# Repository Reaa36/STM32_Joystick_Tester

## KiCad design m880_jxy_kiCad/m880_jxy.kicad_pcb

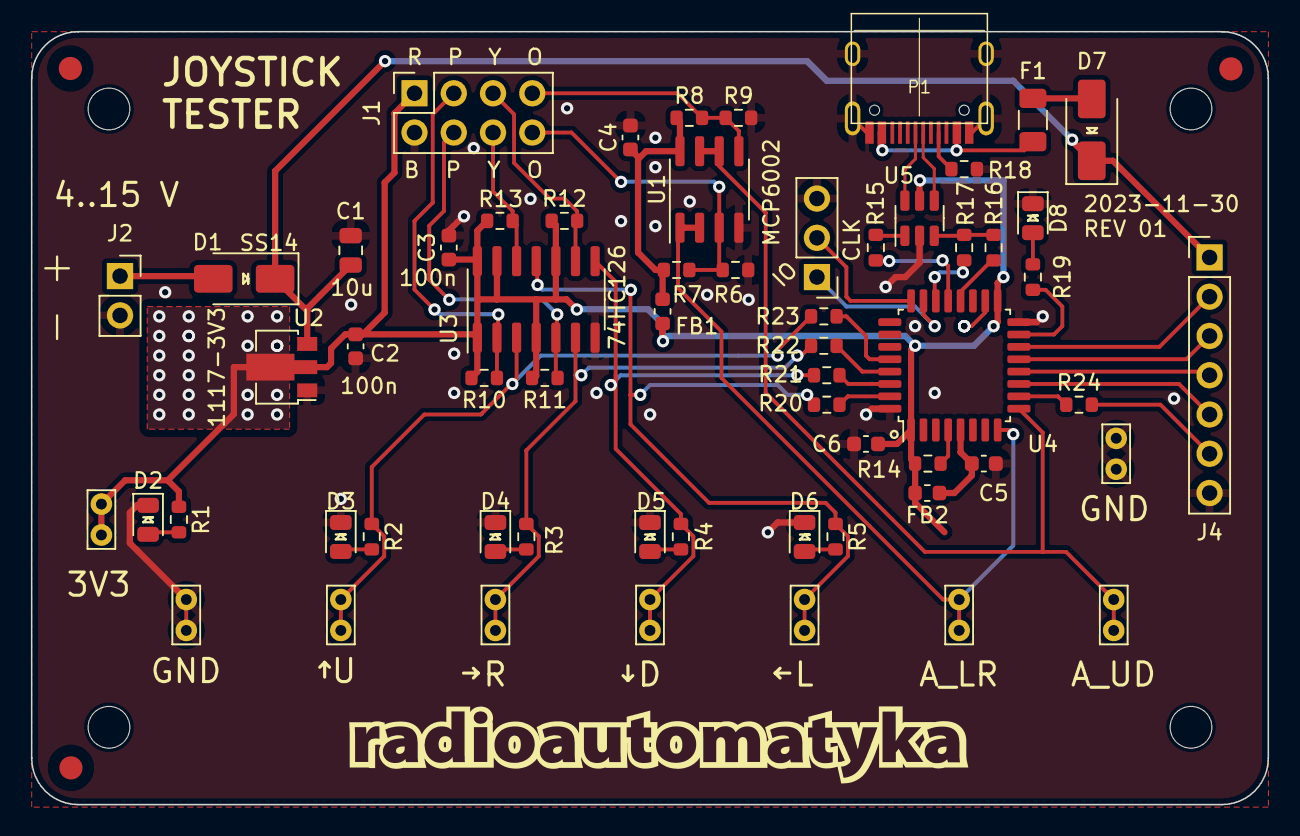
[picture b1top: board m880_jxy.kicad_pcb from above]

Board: 2 copper layers, 80.0 x 50.0 mm, 67 parts (0 on the bottom side), 48 nets.

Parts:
C1: 10u; C_0805_2012Metric
C2, C3, C4, C5, C6: 100n; C_0603_1608Metric
D1, D7: SS14; D_SMA
D2, D3, D4, D5, D6, D8: KT-0805G; LED_0805_2012Metric
F1: Polyfuse; Fuse_1206_3216Metric
FB1, FB2: GZ1608D601TF; L_0603_1608Metric
FID1, FID2, FID3: Fiducial; Fiducial_1.5mm_Mask3mm
H1, H2, H3, H4: MountingHole; MountingHole_2.7mm_M2.5
J1: 280384-2; PinSocket_2x04_P2.54mm_Vertical
J2: POWER; PinSocket_1x02_P2.54mm_Vertical
J3: Conn_01x03; PinHeader_1x03_P2.54mm_Vertical
J4: Conn_01x07; PinHeader_1x07_P2.54mm_Vertical
P1: USB4105-GF-A; TYPE-C-31-M-12
R1, R2, R3, R4, R5, R19, R20, R21, R22, R23: 1k; R_0603_1608Metric
R6, R7, R8, R9, R10, R11, R12, R13: 1M; R_0603_1608Metric
R14, R24: 10k; R_0603_1608Metric
R15, R16: 22; R_0603_1608Metric
R17: 1k5; R_0603_1608Metric
R18: 5k1; R_0603_1608Metric
TP1: C_UP; TestPoint_Bridge_Pitch2.0mm_Drill0.7mm
TP2: C_RIGHT; TestPoint_Bridge_Pitch2.0mm_Drill0.7mm
TP3: C_DOWN; TestPoint_Bridge_Pitch2.0mm_Drill0.7mm
TP4: C_LEFT; TestPoint_Bridge_Pitch2.0mm_Drill0.7mm
TP5: ANA_LR; TestPoint_Bridge_Pitch2.0mm_Drill0.7mm
TP6: ANA_UD; TestPoint_Bridge_Pitch2.0mm_Drill0.7mm
TP7, TP9: GND; TestPoint_Bridge_Pitch2.0mm_Drill0.7mm
TP8: 3V3; TestPoint_Bridge_Pitch2.0mm_Drill0.7mm
U1: MCP6002DRG; SOIC-8_3.9x4.9mm_P1.27mm
U2: AMS1117-3.3; SOT-89-3
U3: 74HC126D,653; SO-14_3.9x8.65mm_P1.27mm
U4: STM32F042K6Tx; LQFP-32_7x7mm_P0.8mm
U5: USBLC6-2SC6; SOT-23-6

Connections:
+3.3VA: C4.1, FB1.2, R7.1, R8.1, U1.8 (V+)
+3V3: C2.1, C3.1, C6.1, FB1.1, FB2.2, J1.1, R1.1, R10.2, R11.2, R12.2, R13.2, R14.1, TP8.1, U2.2 (VO), U3.1, U3.4, U3.10, U3.13, U3.14 (VCC), U4.1 (VDD), U4.17 (VDDIO2), U5.5 (VBUS)
+5V: C1.1, D1.1 (K), D7.1 (K), J4.1, U2.3 (VI)
/ANA_LEFTRIGHT: J1.8, R6.1, R7.2, U1.3 (+)
/ANA_LEFTRIGHT_B: TP5.1, U1.1, U1.2 (-), U4.8 (PA2)
/ANA_UPDOWN: J1.7, R8.2, R9.1, U1.5 (+)
/ANA_UPDOWN_B: TP6.1, U1.6 (-), U1.7, U4.9 (PA3)
/C_DOWN: J1.5, R12.1, U3.9
/C_DOWN_B: R4.1, R21.1, TP3.1, U3.8
/C_LEFT: J1.6, R13.1, U3.12
/C_LEFT_B: R5.1, R20.1, TP4.1, U3.11
/C_RIGHT: J1.4, R11.1, U3.5
/C_RIGHT_B: R3.1, R22.1, TP2.1, U3.6
/C_UP: J1.3, R10.1, U3.2
/C_UP_B: R2.1, R23.1, TP1.1, U3.3
/M880_jxy_STM32_MCU/EXT_PB0: J4.2, U4.14 (PB0)
/M880_jxy_STM32_MCU/LED: R19.1, U4.15 (PB1)
/M880_jxy_STM32_MCU/SYS_SWCLK: J3.2, U4.24 (PA14)
/M880_jxy_STM32_MCU/SYS_SWDIO: J3.1, U4.23 (PA13)
/M880_jxy_STM32_MCU/USB_D+: P1.A6 (D+), U5.4 (I/O2)
/M880_jxy_STM32_MCU/USB_D-: P1.A7 (D-), U5.6 (I/O1)
/M880_jxy_STM32_MCU/USB_ENUM: R17.1, U4.20 (PA10)
/M880_jxy_STM32_MCU/USB__D+: R16.2, U4.22 (PA12)
/M880_jxy_STM32_MCU/USB__D-: R15.2, U4.21 (PA11)
GND: C1.2, C2.2, C3.2, C4.2, C5.2, C6.2, D2.1 (K), D3.1 (K), D4.1 (K), D5.1 (K), D6.1 (K), D8.1 (K), J1.2, J2.2, J3.3, J4.7, P1.A1 (GND), P1.A12 (GND), P1.B1 (GND), P1.B12 (GND), P1.S1 (SHIELD), R6.2, R9.2, R18.2, TP7.1, TP9.1, U1.4 (V-), U2.1 (GND), U3.7 (GND), U4.16 (VSS), U4.32 (VSSA), U5.2 (GND)
unnamed: D1.2 (A), J2.1
unnamed: D2.2 (A), R1.2
unnamed: D3.2 (A), R2.2
unnamed: D4.2 (A), R3.2
unnamed: D5.2 (A), R4.2
unnamed: D6.2 (A), R5.2
unnamed: D7.2 (A), F1.2
unnamed: D8.2 (A), R19.2
unnamed: F1.1, P1.A4 (VBUS), P1.A9 (VBUS), P1.B4 (VBUS), P1.B9 (VBUS)
unnamed: J4.3, U4.13 (PA7)
unnamed: J4.4, U4.12 (PA6)
unnamed: J4.5, U4.11 (PA5)
unnamed: J4.6, R24.2
unnamed: P1.A5 (CC), R18.1
unnamed: R15.1, U5.1 (I/O1)
unnamed: R16.1, R17.2, U5.3 (I/O2)
unnamed: R14.2, U4.4 (NRST)
unnamed: R24.1, U4.10 (PA4)
unnamed: R23.2, U4.28 (PB5)
unnamed: R22.2, U4.29 (PB6)
unnamed: R21.2, U4.30 (PB7)
unnamed: R20.2, U4.31 (PB8)
unnamed: C5.1, FB2.1, U4.5 (VDDA)

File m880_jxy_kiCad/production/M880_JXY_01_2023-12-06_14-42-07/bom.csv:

Designator,Footprint,Quantity,Value,LCSC Part #
C1,0805,1,10u,
"C2, C3, C4, C5, C6",0603,5,100n,
"D1, D7",D_SMA,2,SS14,
"D2, D3, D4, D5, D6, D8",0805,6,KT-0805G,
"FB1, FB2",0603,2,GZ1608D601TF,
"R1, R19, R2, R20, R21, R22, R23, R3, R4, R5",0603,10,1k,
"R10, R11, R12, R13, R6, R7, R8, R9",0603,8,1M,
"R14, R24",0603,2,10k,
"R15, R16",0603,2,22,
R17,0603,1,1k5,
R18,0603,1,5k1,
U1,SOIC-8_3.9x4.9mm_P1.27mm,1,MCP6002DRG,
U2,SOT-89-3,1,AMS1117-3.3,
U3,SO-14_3.9x8.65mm_P1.27mm,1,"74HC126D,653",

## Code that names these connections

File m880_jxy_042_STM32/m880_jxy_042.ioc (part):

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Mcu.Name=STM32F042K(4-6)Tx
Mcu.Package=LQFP32
Mcu.UserName=STM32F042K6Tx
PA10.GPIOParameters=GPIO_Label
PA10.GPIO_Label=USB_REEN
PA10.Signal=GPIO_Output
PA11.Mode=Device
PA11.Signal=USB_DM
PA12.Mode=Device
PA12.Signal=USB_DP
PA13.Mode=Serial_Wire
PA13.Signal=SYS_SWDIO
PA14.Mode=Serial_Wire
PA14.Signal=SYS_SWCLK
PA2.Mode=IN2
PA2.Signal=ADC_IN2
PA3.Mode=IN3
PA3.Signal=ADC_IN3
PB1.GPIOParameters=GPIO_Label
PB1.GPIO_Label=LED
PB1.Signal=GPIO_Output
PB5.GPIOParameters=GPIO_Label
PB5.GPIO_Label=UP
PB5.Signal=GPIO_Input
PB6.GPIOParameters=GPIO_Label
PB6.GPIO_Label=RIGHT
PB6.Signal=GPIO_Input
PB7.GPIOParameters=GPIO_Label
PB7.GPIO_Label=DOWN
PB7.Signal=GPIO_Input
PB8.GPIOParameters=GPIO_Label
PB8.GPIO_Label=LEFT
PB8.Signal=GPIO_Input
RCC.SYSCLKFreq_VALUE=48000000
RCC.SYSCLKSource=RCC_SYSCLKSOURCE_HSI48
board=custom

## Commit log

2024-07-31 The first commit
